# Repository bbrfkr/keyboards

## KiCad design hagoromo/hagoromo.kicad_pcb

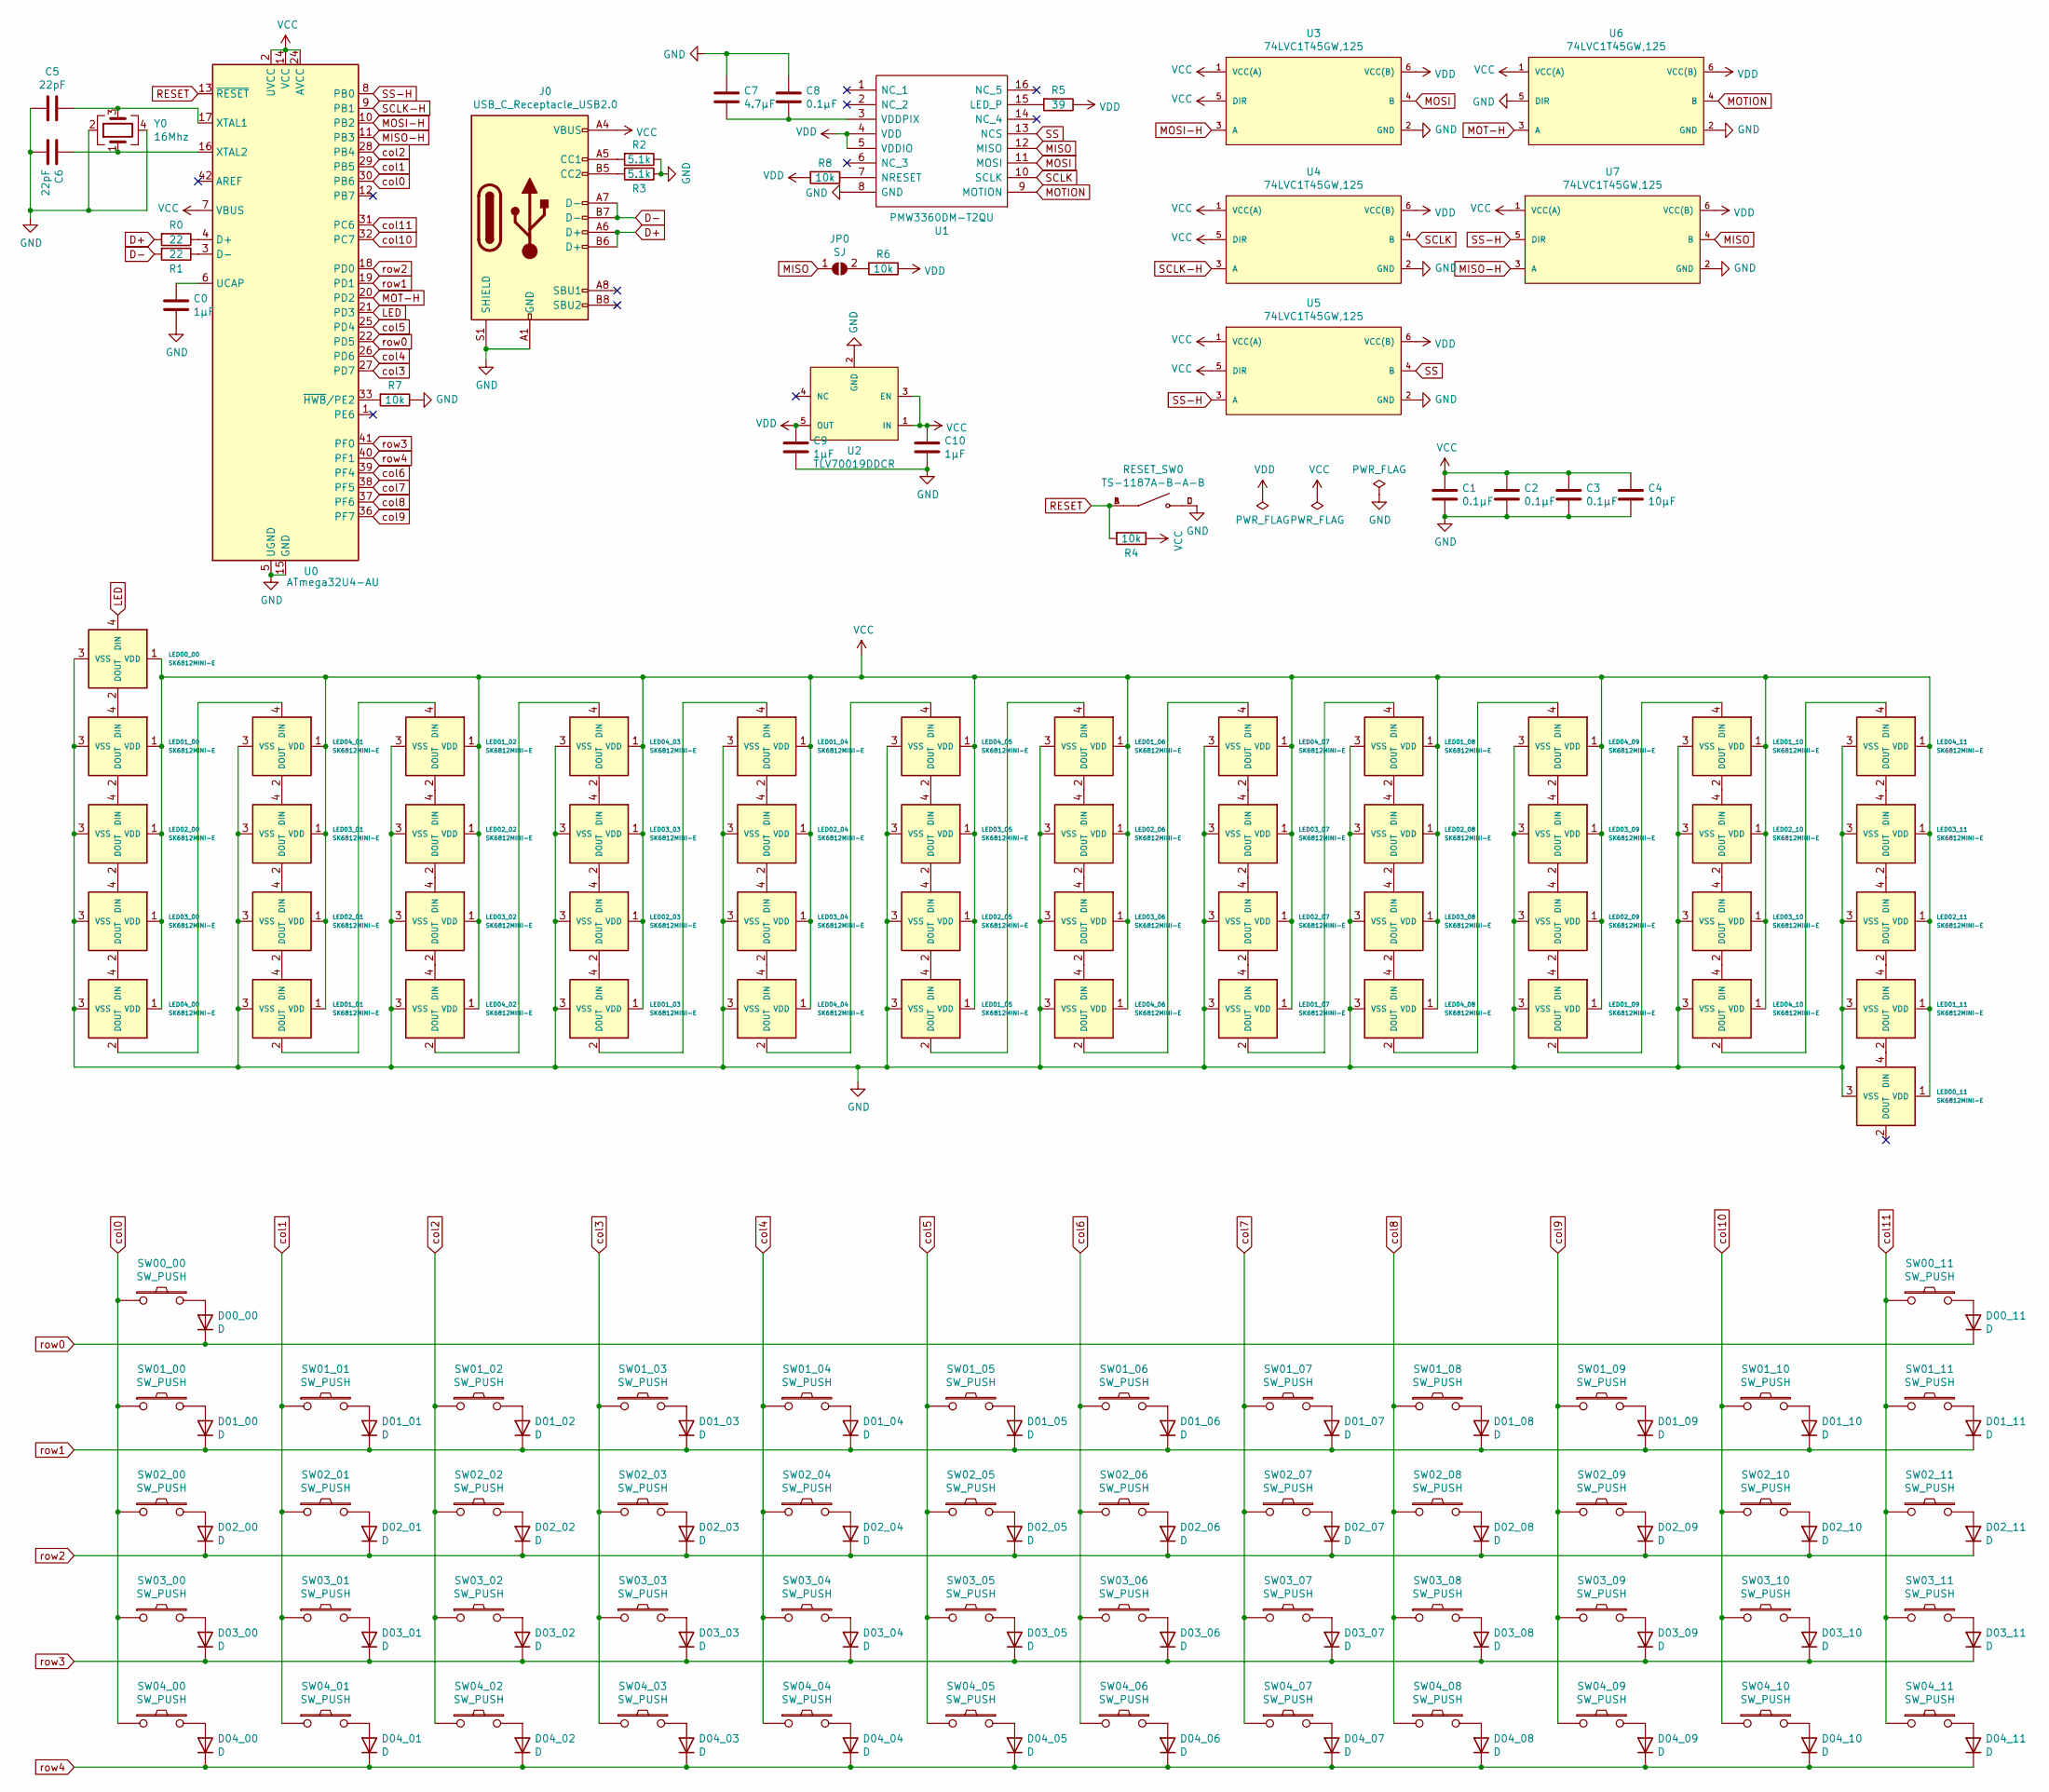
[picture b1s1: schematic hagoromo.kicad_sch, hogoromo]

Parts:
C0, C9, C10: 1μF; C_1206_3216Metric
C1, C2, C3, C8: 0.1μF; C_1206_3216Metric
C4: 10μF; C_1206_3216Metric
C5, C6: 22pF; C_1206_3216Metric
C7: 4.7μF; C_1206_3216Metric
D00_00, D00_11, D01_00, D01_01, D01_02, D01_03, D01_04, D01_05, D01_06, D01_07, D01_08, D01_09, D01_10, D01_11, D02_00, D02_01, D02_02, D02_03, D02_04, D02_05, D02_06, D02_07, D02_08, D02_09, D02_10, D02_11, D03_00, D03_01, D03_02, D03_03, D03_04, D03_05, D03_06, D03_07, D03_08, D03_09, D03_10, D03_11, D04_00, D04_01, D04_02, D04_03, D04_04, D04_05, D04_06, D04_07, D04_08, D04_09, D04_10, D04_11: D; D_SOD-123
J0: USB_C_Receptacle_USB2.0; USB_C_Receptacle_HRO_TYPE-C-31-M-12
JP0: SJ; SolderJumper-2_P1.3mm_Open_Pad1.0x1.5mm
LED00_00, LED00_11, LED01_00, LED01_01, LED01_02, LED01_03, LED01_04, LED01_05, LED01_06, LED01_07, LED01_08, LED01_09, LED01_10, LED01_11, LED02_00, LED02_01, LED02_02, LED02_03, LED02_04, LED02_05, LED02_06, LED02_07, LED02_08, LED02_09, LED02_10, LED02_11, LED03_00, LED03_01, LED03_02, LED03_03, LED03_04, LED03_05, LED03_06, LED03_07, LED03_08, LED03_09, LED03_10, LED03_11, LED04_00, LED04_01, LED04_02, LED04_03, LED04_04, LED04_05, LED04_06, LED04_07, LED04_08, LED04_09, LED04_10, LED04_11: SK6812MINI-E; SK6812-MINI-E
R0, R1: 22; R_1206_3216Metric
R2, R3: 5.1k; R_1206_3216Metric
R4, R6, R7, R8: 10k; R_1206_3216Metric
R5: 39; R_1206_3216Metric
RESET_SW0: TS-1187A-B-A-B; SW_TS-1187A-B-A-B; PARTREV A0
SW00_00, SW00_11, SW01_01, SW01_02, SW01_03, SW01_04, SW01_05, SW01_06, SW01_07, SW01_08, SW01_09, SW01_10, SW02_01, SW02_02, SW02_03, SW02_04, SW02_05, SW02_06, SW02_07, SW02_08, SW02_09, SW02_10, SW03_01, SW03_02, SW03_03, SW03_04, SW03_05, SW03_06, SW03_07, SW03_08, SW03_09, SW03_10, SW04_03, SW04_04, SW04_05, SW04_06, SW04_07, SW04_08: SW_PUSH; SW_Hotswap_Kailh_1.00u
SW01_00, SW01_11: SW_PUSH; SW_Hotswap_Kailh_1.50u
SW02_00: SW_PUSH; SW_Hotswap_Kailh_1.75u
SW02_11, SW03_00: SW_PUSH; SW_Hotswap_Kailh_2.25u
SW03_11: SW_PUSH; SW_Hotswap_Kailh_2.75u
SW04_00, SW04_01, SW04_02, SW04_09, SW04_10, SW04_11: SW_PUSH; SW_Hotswap_Kailh_1.25u
U0: ATmega32U4-AU; TQFP-44_10x10mm_P0.8mm
U1: PMW3360DM-T2QU; PMW3360; Manufacturer_Part_Number PMW3360DM-T2QU
U2: TLV70019DDCR; Texas_Instruments-TLV70019DDCR-Level_A
U3, U4, U5, U6, U7: 74LVC1T45GW,125; Nexperia-SOT363-11_2018-0-IPC_A; mouser part number 771-74LVC1T45GW125; digikey description IC TRNSLTR BIDIRECTIONAL 6TSSOP
Y0: 16Mhz; Crystal_SMD_SeikoEpson_FA238-4Pin_3.2x2.5mm

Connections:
D+: J0.A6 (D+), J0.B6 (D+), R0.2
D-: J0.A7 (D-), J0.B7 (D-), R1.2
GND: C0.2, C1.2, C2.2, C3.2, C4.2, C5.1, C6.2, C7.1, C8.1, C9.2, C10.2, J0.A1 (GND), J0.A12 (GND), J0.B1 (GND), J0.B12 (GND), J0.S1 (SHIELD), LED00_00.3 (VSS), LED00_11.3 (VSS), LED01_00.3 (VSS), LED01_01.3 (VSS), LED01_02.3 (VSS), LED01_03.3 (VSS), LED01_04.3 (VSS), LED01_05.3 (VSS), LED01_06.3 (VSS), LED01_07.3 (VSS), LED01_08.3 (VSS), LED01_09.3 (VSS), LED01_10.3 (VSS), LED01_11.3 (VSS), LED02_00.3 (VSS), LED02_01.3 (VSS), LED02_02.3 (VSS), LED02_03.3 (VSS), LED02_04.3 (VSS), LED02_05.3 (VSS), LED02_06.3 (VSS), LED02_07.3 (VSS), LED02_08.3 (VSS), LED02_09.3 (VSS), LED02_10.3 (VSS), LED02_11.3 (VSS), LED03_00.3 (VSS), LED03_01.3 (VSS), LED03_02.3 (VSS), LED03_03.3 (VSS), LED03_04.3 (VSS), LED03_05.3 (VSS), LED03_06.3 (VSS), LED03_07.3 (VSS), LED03_08.3 (VSS), LED03_09.3 (VSS), LED03_10.3 (VSS), LED03_11.3 (VSS), LED04_00.3 (VSS), LED04_01.3 (VSS), LED04_02.3 (VSS), LED04_03.3 (VSS), LED04_04.3 (VSS), LED04_05.3 (VSS), LED04_06.3 (VSS), LED04_07.3 (VSS), LED04_08.3 (VSS), LED04_09.3 (VSS), LED04_10.3 (VSS), LED04_11.3 (VSS), R2.1, R3.1, R7.1, RESET_SW0.C, RESET_SW0.D, U0.5 (UGND), U0.15 (GND), U0.23 (GND), U0.35 (GND), U0.43 (GND), U1.8 (GND), U2.2 (GND), U3.2 (GND), U4.2 (GND), U5.2 (GND), U6.2 (GND), U6.5 (DIR), U7.2 (GND), Y0.2, Y0.4
LED: LED00_00.4 (DIN), U0.21 (PD3)
MISO: JP0.1 (A), U1.12 (MISO), U7.4 (B)
MISO-H: U0.11 (PB3), U7.3 (A)
MOSI: U1.11 (MOSI), U3.4 (B)
MOSI-H: U0.10 (PB2), U3.3 (A)
MOT-H: U0.20 (PD2), U6.3 (A)
MOTION: U1.9 (MOTION), U6.4 (B)
unnamed: C0.1, U0.6 (UCAP)
unnamed: C5.2, U0.17 (XTAL1), Y0.3
unnamed: C6.1, U0.16 (XTAL2), Y0.1
unnamed: C7.2, C8.2, U1.3 (VDDPIX)
unnamed: D00_00.2 (A), SW00_00.2
unnamed: D00_11.2 (A), SW00_11.2
unnamed: D01_00.2 (A), SW01_00.2
unnamed: D01_01.2 (A), SW01_01.2
unnamed: D01_02.2 (A), SW01_02.2
unnamed: D01_03.2 (A), SW01_03.2
unnamed: D01_04.2 (A), SW01_04.2
unnamed: D01_05.2 (A), SW01_05.2
unnamed: D01_06.2 (A), SW01_06.2
unnamed: D01_07.2 (A), SW01_07.2
unnamed: D01_08.2 (A), SW01_08.2
unnamed: D01_09.2 (A), SW01_09.2
unnamed: D01_10.2 (A), SW01_10.2
unnamed: D01_11.2 (A), SW01_11.2
unnamed: D02_00.2 (A), SW02_00.2
unnamed: D02_01.2 (A), SW02_01.2
unnamed: D02_02.2 (A), SW02_02.2
unnamed: D02_03.2 (A), SW02_03.2
unnamed: D02_04.2 (A), SW02_04.2
unnamed: D02_05.2 (A), SW02_05.2
unnamed: D02_06.2 (A), SW02_06.2
unnamed: D02_07.2 (A), SW02_07.2
unnamed: D02_08.2 (A), SW02_08.2
unnamed: D02_09.2 (A), SW02_09.2
unnamed: D02_10.2 (A), SW02_10.2
unnamed: D02_11.2 (A), SW02_11.2
unnamed: D03_00.2 (A), SW03_00.2
unnamed: D03_01.2 (A), SW03_01.2
unnamed: D03_02.2 (A), SW03_02.2
unnamed: D03_03.2 (A), SW03_03.2
unnamed: D03_04.2 (A), SW03_04.2
unnamed: D03_05.2 (A), SW03_05.2
unnamed: D03_06.2 (A), SW03_06.2
unnamed: D03_07.2 (A), SW03_07.2
unnamed: D03_08.2 (A), SW03_08.2
unnamed: D03_09.2 (A), SW03_09.2
unnamed: D03_10.2 (A), SW03_10.2
unnamed: D03_11.2 (A), SW03_11.2
unnamed: D04_00.2 (A), SW04_00.2
unnamed: D04_01.2 (A), SW04_01.2
unnamed: D04_02.2 (A), SW04_02.2
unnamed: D04_03.2 (A), SW04_03.2
unnamed: D04_04.2 (A), SW04_04.2
unnamed: D04_05.2 (A), SW04_05.2
unnamed: D04_06.2 (A), SW04_06.2
unnamed: D04_07.2 (A), SW04_07.2
unnamed: D04_08.2 (A), SW04_08.2
unnamed: D04_09.2 (A), SW04_09.2
unnamed: D04_10.2 (A), SW04_10.2
unnamed: D04_11.2 (A), SW04_11.2
unnamed: J0.A5 (CC1), R2.2
unnamed: J0.B5 (CC2), R3.2
unnamed: JP0.2 (B), R6.2
unnamed: LED00_00.2 (DOUT), LED01_00.4 (DIN)
unnamed: LED00_11.4 (DIN), LED01_11.2 (DOUT)
unnamed: LED01_00.2 (DOUT), LED02_00.4 (DIN)
unnamed: LED01_01.2 (DOUT), LED01_02.4 (DIN)
unnamed: LED01_01.4 (DIN), LED02_01.2 (DOUT)
unnamed: LED01_02.2 (DOUT), LED02_02.4 (DIN)
unnamed: LED01_03.2 (DOUT), LED01_04.4 (DIN)
unnamed: LED01_03.4 (DIN), LED02_03.2 (DOUT)
unnamed: LED01_04.2 (DOUT), LED02_04.4 (DIN)
unnamed: LED01_05.2 (DOUT), LED01_06.4 (DIN)
unnamed: LED01_05.4 (DIN), LED02_05.2 (DOUT)
unnamed: LED01_06.2 (DOUT), LED02_06.4 (DIN)
unnamed: LED01_07.2 (DOUT), LED01_08.4 (DIN)
unnamed: LED01_07.4 (DIN), LED02_07.2 (DOUT)
unnamed: LED01_08.2 (DOUT), LED02_08.4 (DIN)
unnamed: LED01_09.2 (DOUT), LED01_10.4 (DIN)
unnamed: LED01_09.4 (DIN), LED02_09.2 (DOUT)
unnamed: LED01_10.2 (DOUT), LED02_10.4 (DIN)
unnamed: LED01_11.4 (DIN), LED02_11.2 (DOUT)
unnamed: LED02_00.2 (DOUT), LED03_00.4 (DIN)
unnamed: LED02_01.4 (DIN), LED03_01.2 (DOUT)
unnamed: LED02_02.2 (DOUT), LED03_02.4 (DIN)
unnamed: LED02_03.4 (DIN), LED03_03.2 (DOUT)
unnamed: LED02_04.2 (DOUT), LED03_04.4 (DIN)
unnamed: LED02_05.4 (DIN), LED03_05.2 (DOUT)
unnamed: LED02_06.2 (DOUT), LED03_06.4 (DIN)
unnamed: LED02_07.4 (DIN), LED03_07.2 (DOUT)
unnamed: LED02_08.2 (DOUT), LED03_08.4 (DIN)
unnamed: LED02_09.4 (DIN), LED03_09.2 (DOUT)
unnamed: LED02_10.2 (DOUT), LED03_10.4 (DIN)
unnamed: LED02_11.4 (DIN), LED03_11.2 (DOUT)
unnamed: LED03_00.2 (DOUT), LED04_00.4 (DIN)
unnamed: LED03_01.4 (DIN), LED04_01.2 (DOUT)
unnamed: LED03_02.2 (DOUT), LED04_02.4 (DIN)
unnamed: LED03_03.4 (DIN), LED04_03.2 (DOUT)
unnamed: LED03_04.2 (DOUT), LED04_04.4 (DIN)
unnamed: LED03_05.4 (DIN), LED04_05.2 (DOUT)
unnamed: LED03_06.2 (DOUT), LED04_06.4 (DIN)
unnamed: LED03_07.4 (DIN), LED04_07.2 (DOUT)
unnamed: LED03_08.2 (DOUT), LED04_08.4 (DIN)
unnamed: LED03_09.4 (DIN), LED04_09.2 (DOUT)
unnamed: LED03_10.2 (DOUT), LED04_10.4 (DIN)
unnamed: LED03_11.4 (DIN), LED04_11.2 (DOUT)
unnamed: LED04_00.2 (DOUT), LED04_01.4 (DIN)
unnamed: LED04_02.2 (DOUT), LED04_03.4 (DIN)
unnamed: LED04_04.2 (DOUT), LED04_05.4 (DIN)
unnamed: LED04_06.2 (DOUT), LED04_07.4 (DIN)
unnamed: LED04_08.2 (DOUT), LED04_09.4 (DIN)
unnamed: LED04_10.2 (DOUT), LED04_11.4 (DIN)
unnamed: R0.1, U0.4 (D+)
unnamed: R1.1, U0.3 (D-)
unnamed: R5.2, U1.15 (LED_P)
unnamed: R7.2, U0.33 (~HWB/PE2)
unnamed: R8.1, U1.7 (NRESET)
RESET: R4.2, RESET_SW0.A, RESET_SW0.B, U0.13 (~RESET)
SCLK: U1.10 (SCLK), U4.4 (B)
SCLK-H: U0.9 (PB1), U4.3 (A)
SS: U1.13 (NCS), U5.4 (B)
SS-H: U0.8 (PB0), U5.3 (A), U7.5 (DIR)
VCC: C1.1, C2.1, C3.1, C4.1, C10.1, J0.A4 (VBUS), J0.A9 (VBUS), J0.B4 (VBUS), J0.B9 (VBUS), LED00_00.1 (VDD), LED00_11.1 (VDD), LED01_00.1 (VDD), LED01_01.1 (VDD), LED01_02.1 (VDD), LED01_03.1 (VDD), LED01_04.1 (VDD), LED01_05.1 (VDD), LED01_06.1 (VDD), LED01_07.1 (VDD), LED01_08.1 (VDD), LED01_09.1 (VDD), LED01_10.1 (VDD), LED01_11.1 (VDD), LED02_00.1 (VDD), LED02_01.1 (VDD), LED02_02.1 (VDD), LED02_03.1 (VDD), LED02_04.1 (VDD), LED02_05.1 (VDD), LED02_06.1 (VDD), LED02_07.1 (VDD), LED02_08.1 (VDD), LED02_09.1 (VDD), LED02_10.1 (VDD), LED02_11.1 (VDD), LED03_00.1 (VDD), LED03_01.1 (VDD), LED03_02.1 (VDD), LED03_03.1 (VDD), LED03_04.1 (VDD), LED03_05.1 (VDD), LED03_06.1 (VDD), LED03_07.1 (VDD), LED03_08.1 (VDD), LED03_09.1 (VDD), LED03_10.1 (VDD), LED03_11.1 (VDD), LED04_00.1 (VDD), LED04_01.1 (VDD), LED04_02.1 (VDD), LED04_03.1 (VDD), LED04_04.1 (VDD), LED04_05.1 (VDD), LED04_06.1 (VDD), LED04_07.1 (VDD), LED04_08.1 (VDD), LED04_09.1 (VDD), LED04_10.1 (VDD), LED04_11.1 (VDD), R4.1, U0.2 (UVCC), U0.7 (VBUS), U0.14 (VCC), U0.24 (AVCC), U0.34 (VCC), U0.44 (AVCC), U2.1 (IN), U2.3 (EN), U3.1 (VCC(A)), U3.5 (DIR), U4.1 (VCC(A)), U4.5 (DIR), U5.1 (VCC(A)), U5.5 (DIR), U6.1 (VCC(A)), U7.1 (VCC(A))
VDD: C9.1, R5.1, R6.1, R8.2, U1.4 (VDD), U1.5 (VDDIO), U2.5 (OUT), U3.6 (VCC(B)), U4.6 (VCC(B)), U5.6 (VCC(B)), U6.6 (VCC(B)), U7.6 (VCC(B))
col0: SW00_00.1, SW01_00.1, SW02_00.1, SW03_00.1, SW04_00.1, U0.30 (PB6)
col1: SW01_01.1, SW02_01.1, SW03_01.1, SW04_01.1, U0.29 (PB5)
col2: SW01_02.1, SW02_02.1, SW03_02.1, SW04_02.1, U0.28 (PB4)
col3: SW01_03.1, SW02_03.1, SW03_03.1, SW04_03.1, U0.27 (PD7)
col4: SW01_04.1, SW02_04.1, SW03_04.1, SW04_04.1, U0.26 (PD6)
col5: SW01_05.1, SW02_05.1, SW03_05.1, SW04_05.1, U0.25 (PD4)
col6: SW01_06.1, SW02_06.1, SW03_06.1, SW04_06.1, U0.39 (PF4)
col7: SW01_07.1, SW02_07.1, SW03_07.1, SW04_07.1, U0.38 (PF5)
col8: SW01_08.1, SW02_08.1, SW03_08.1, SW04_08.1, U0.37 (PF6)
col9: SW01_09.1, SW02_09.1, SW03_09.1, SW04_09.1, U0.36 (PF7)
col10: SW01_10.1, SW02_10.1, SW03_10.1, SW04_10.1, U0.32 (PC7)
col11: SW00_11.1, SW01_11.1, SW02_11.1, SW03_11.1, SW04_11.1, U0.31 (PC6)
row0: D00_00.1 (K), D00_11.1 (K), U0.22 (PD5)
row1: D01_00.1 (K), D01_01.1 (K), D01_02.1 (K), D01_03.1 (K), D01_04.1 (K), D01_05.1 (K), D01_06.1 (K), D01_07.1 (K), D01_08.1 (K), D01_09.1 (K), D01_10.1 (K), D01_11.1 (K), U0.19 (PD1)
row2: D02_00.1 (K), D02_01.1 (K), D02_02.1 (K), D02_03.1 (K), D02_04.1 (K), D02_05.1 (K), D02_06.1 (K), D02_07.1 (K), D02_08.1 (K), D02_09.1 (K), D02_10.1 (K), D02_11.1 (K), U0.18 (PD0)
row3: D03_00.1 (K), D03_01.1 (K), D03_02.1 (K), D03_03.1 (K), D03_04.1 (K), D03_05.1 (K), D03_06.1 (K), D03_07.1 (K), D03_08.1 (K), D03_09.1 (K), D03_10.1 (K), D03_11.1 (K), U0.41 (PF0)
row4: D04_00.1 (K), D04_01.1 (K), D04_02.1 (K), D04_03.1 (K), D04_04.1 (K), D04_05.1 (K), D04_06.1 (K), D04_07.1 (K), D04_08.1 (K), D04_09.1 (K), D04_10.1 (K), D04_11.1 (K), U0.40 (PF1)

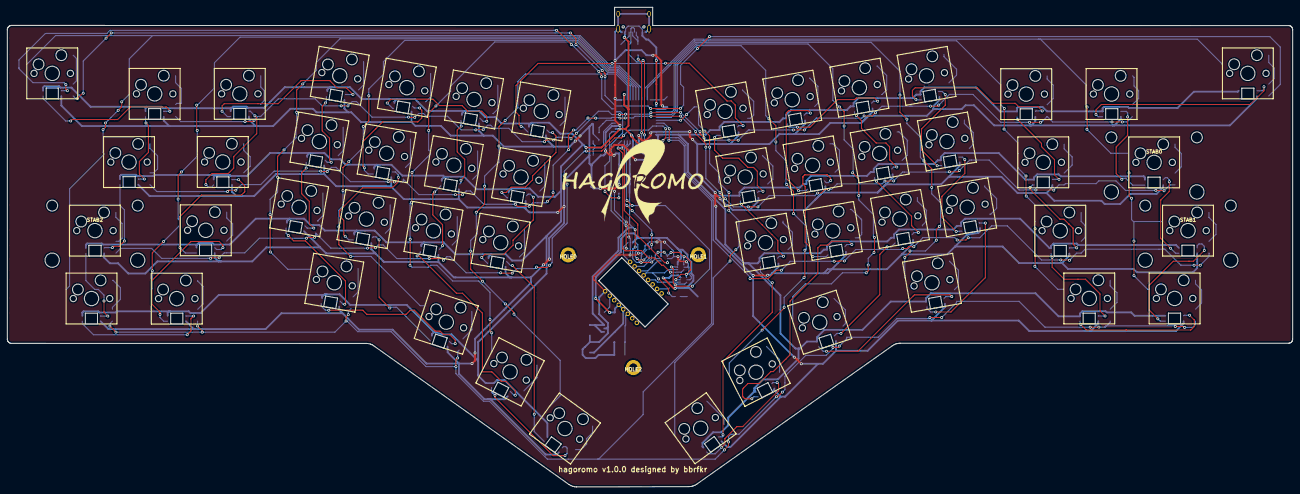
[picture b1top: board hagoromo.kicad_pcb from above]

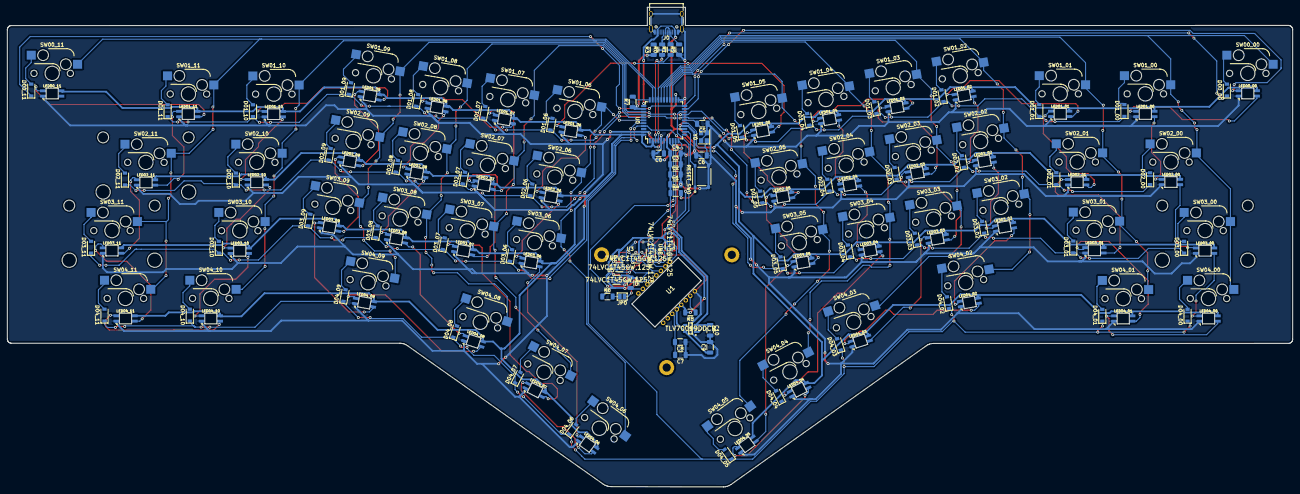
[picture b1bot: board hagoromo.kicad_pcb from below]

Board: 2 copper layers, 358.9 x 133.9 mm, 189 parts (132 on the bottom side), 145 nets.

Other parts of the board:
HOLE0, HOLE1, HOLE2: M2_Hole_TH
LOGO0: LOGO; logo
STAB0, STAB1, STAB2: Stabilizer_Cherry_MX_2u

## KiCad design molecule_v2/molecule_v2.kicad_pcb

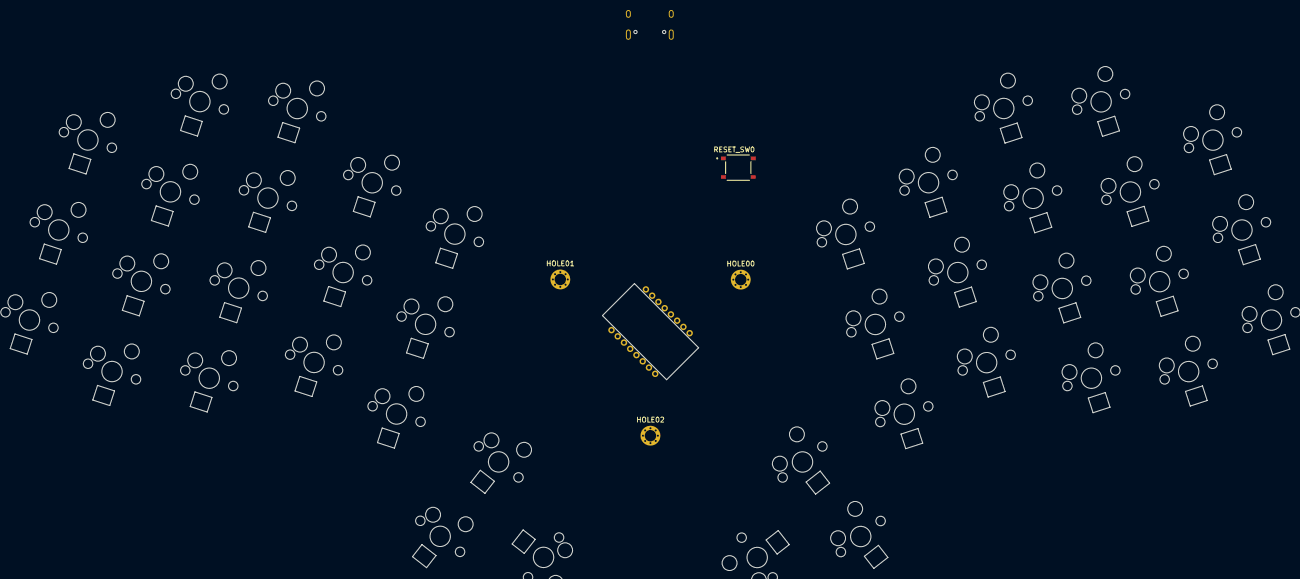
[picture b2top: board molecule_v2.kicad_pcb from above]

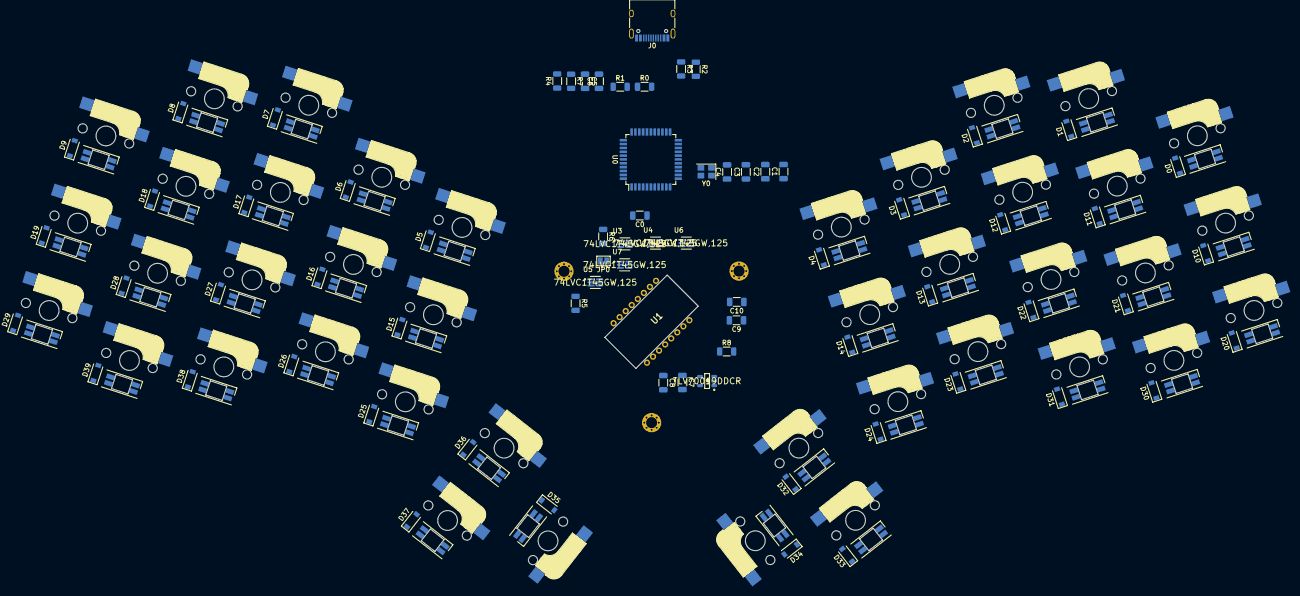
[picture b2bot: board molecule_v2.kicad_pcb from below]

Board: 2 copper layers, 156 parts (111 on the bottom side), 122 nets, no tracks yet.

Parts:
C0, C9, C10: 1μF; C_1206_3216Metric
C1, C2, C3, C8: 0.1μF; C_1206_3216Metric
C4: 10μF; C_1206_3216Metric
C5, C6: 22pF; C_1206_3216Metric
C7: 4.7μF; C_1206_3216Metric
D0, D1, D2, D3, D4, D5, D6, D7, D8, D9, D10, D11, D12, D13, D14, D15, D16, D17, D18, D19, D20, D21, D22, D23, D24, D25, D26, D27, D28, D29, D30, D31, D32, D33, D34, D35, D36, D37, D38, D39: D; D_SOD-123
HOLE00, HOLE01, HOLE02: Val**; M2_HOLE_v3
J0: USB_C_Receptacle_USB2.0; USB_C_Receptacle_HRO_TYPE-C-31-M-12
JP0: SJ; SolderJumper-2_P1.3mm_Open_Pad1.0x1.5mm
LED0, LED1, LED2, LED3, LED4, LED5, LED6, LED7, LED8, LED9, LED10, LED11, LED12, LED13, LED14, LED15, LED16, LED17, LED18, LED19, LED20, LED21, LED22, LED23, LED24, LED25, LED26, LED27, LED28, LED29, LED30, LED31, LED32, LED33, LED34, LED35, LED36, LED37, LED38, LED39: YS-SK6812MINI-E
LOGO01: LOGO; molecule-logo
R0, R1: 22; R_1206_3216Metric
R2, R3: 5.1k; R_1206_3216Metric
R4, R6, R7, R8: 10k; R_1206_3216Metric
R5: 39; R_1206_3216Metric
RESET_SW0: TS-1187A-B-A-B; SW_TS-1187A-B-A-B
SW0, SW1, SW2, SW3, SW4, SW5, SW6, SW7, SW8, SW9, SW10, SW11, SW12, SW13, SW14, SW15, SW16, SW17, SW18, SW19, SW20, SW21, SW22, SW23, SW24, SW25, SW26, SW27, SW28, SW29, SW30, SW31, SW32, SW33, SW36, SW37, SW38, SW39: SW_PUSH; CherryMX_Hotswap
SW34, SW35: SW_PUSH; CherryMX_Hotswap_1.5u
U0: ATmega32U4-AU; TQFP-44_10x10mm_P0.8mm
U1: PMW3360DM-T2QU; PMW3360
U2: TLV70019DDCR; Texas_Instruments-TLV70019DDCR-Level_A
U3, U4, U5, U6, U7: 74LVC1T45GW,125; Nexperia-SOT363-11_2018-0-IPC_A
Y0: 16Mhz; Crystal_SMD_SeikoEpson_FA238-4Pin_3.2x2.5mm

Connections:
D+: J0.A6, J0.B6, R0.2
D-: J0.A7, J0.B7, R1.2
GND: C0.2, C1.2, C2.2, C3.2, C4.2, C5.1, C6.2, C7.1, C8.1, C9.2, C10.2, J0.A1, J0.A12, J0.B1, J0.B12, J0.S1, LED0.3, LED1.3, LED2.3, LED3.3, LED4.3, LED5.3, LED6.3, LED7.3, LED8.3, LED9.3, LED10.3, LED11.3, LED12.3, LED13.3, LED14.3, LED15.3, LED16.3, LED17.3, LED18.3, LED19.3, LED20.3, LED21.3, LED22.3, LED23.3, LED24.3, LED25.3, LED26.3, LED27.3, LED28.3, LED29.3, LED30.3, LED31.3, LED32.3, LED33.3, LED34.3, LED35.3, LED36.3, LED37.3, LED38.3, LED39.3, R2.1, R3.1, R7.1, RESET_SW0.C, RESET_SW0.D, U0.5, U0.15, U0.23, U0.35, U0.43, U1.8, U2.2, U3.2, U4.2, U5.2, U6.2, U6.5, U7.2, Y0.2, Y0.4
LED: LED0.4, U0.21
MISO: JP0.1, U1.12, U7.4
MISO-H: U0.11, U7.3
MOSI: U1.11, U3.4
MOSI-H: U0.10, U3.3
MOT-H: U0.20, U6.3
MOTION: U1.9, U6.4
unnamed: C0.1, U0.6
unnamed: C5.2, U0.17, Y0.3
unnamed: C6.1, U0.16, Y0.1
unnamed: C7.2, C8.2, U1.3
unnamed: D0.2, SW0.2
unnamed: D1.2, SW1.2
unnamed: D2.2, SW2.2
unnamed: D3.2, SW3.2
unnamed: D4.2, SW4.2
unnamed: D5.2, SW5.2
unnamed: D6.2, SW6.2
unnamed: D7.2, SW7.2
unnamed: D8.2, SW8.2
unnamed: D9.2, SW9.2
unnamed: D10.2, SW10.2
unnamed: D11.2, SW11.2
unnamed: D12.2, SW12.2
unnamed: D13.2, SW13.2
unnamed: D14.2, SW14.2
unnamed: D15.2, SW15.2
unnamed: D16.2, SW16.2
unnamed: D17.2, SW17.2
unnamed: D18.2, SW18.2
unnamed: D19.2, SW19.2
unnamed: D20.2, SW20.2
unnamed: D21.2, SW21.2
unnamed: D22.2, SW22.2
unnamed: D23.2, SW23.2
unnamed: D24.2, SW24.2
unnamed: D25.2, SW25.2
unnamed: D26.2, SW26.2
unnamed: D27.2, SW27.2
unnamed: D28.2, SW28.2
unnamed: D29.2, SW29.2
unnamed: D30.2, SW30.2
unnamed: D31.2, SW31.2
unnamed: D32.2, SW32.2
unnamed: D33.2, SW33.2
unnamed: D34.2, SW34.2
unnamed: D35.2, SW35.2
unnamed: D36.2, SW36.2
unnamed: D37.2, SW37.2
unnamed: D38.2, SW38.2
unnamed: D39.2, SW39.2
unnamed: J0.A5, R2.2
unnamed: J0.B5, R3.2
unnamed: JP0.2, R6.2
unnamed: LED0.2, LED10.4
unnamed: LED1.2, LED2.4
unnamed: LED1.4, LED11.2
unnamed: LED3.2, LED4.4
unnamed: LED5.2, LED6.4
unnamed: LED7.2, LED8.4
unnamed: LED10.2, LED20.4
unnamed: LED11.4, LED21.2
unnamed: LED12.2, LED22.4
unnamed: LED2.2, LED12.4
unnamed: LED3.4, LED13.2
unnamed: LED13.4, LED23.2
unnamed: LED14.2, LED24.4
unnamed: LED4.2, LED14.4
unnamed: LED5.4, LED15.2
unnamed: LED15.4, LED25.2
unnamed: LED16.2, LED26.4
unnamed: LED6.2, LED16.4
unnamed: LED7.4, LED17.2
unnamed: LED17.4, LED27.2
unnamed: LED18.2, LED28.4
unnamed: LED8.2, LED18.4
unnamed: LED9.4, LED19.2
unnamed: LED19.4, LED29.2
unnamed: LED20.2, LED30.4
unnamed: LED21.4, LED31.2
unnamed: LED22.2, LED32.4
unnamed: LED23.4, LED33.2
unnamed: LED24.2, LED34.4
unnamed: LED25.4, LED35.2
unnamed: LED26.2, LED36.4
unnamed: LED27.4, LED37.2
unnamed: LED28.2, LED38.4
unnamed: LED29.4, LED39.2
unnamed: LED30.2, LED31.4
unnamed: LED32.2, LED33.4
unnamed: LED34.2, LED35.4
unnamed: LED36.2, LED37.4
unnamed: LED38.2, LED39.4
unnamed: R0.1, U0.4
unnamed: R1.1, U0.3
unnamed: R5.2, U1.15
unnamed: R7.2, U0.33
unnamed: R8.1, U1.7
RESET: R4.2, RESET_SW0.A, RESET_SW0.B, U0.13
SCLK: U1.10, U4.4
SCLK-H: U0.9, U4.3
SS: U1.13, U5.4
SS-H: U0.8, U5.3, U7.5
VCC: C1.1, C2.1, C3.1, C4.1, C10.1, J0.A4, J0.A9, J0.B4, J0.B9, LED0.1, LED1.1, LED2.1, LED3.1, LED4.1, LED5.1, LED6.1, LED7.1, LED8.1, LED9.1, LED10.1, LED11.1, LED12.1, LED13.1, LED14.1, LED15.1, LED16.1, LED17.1, LED18.1, LED19.1, LED20.1, LED21.1, LED22.1, LED23.1, LED24.1, LED25.1, LED26.1, LED27.1, LED28.1, LED29.1, LED30.1, LED31.1, LED32.1, LED33.1, LED34.1, LED35.1, LED36.1, LED37.1, LED38.1, LED39.1, R4.1, U0.2, U0.7, U0.14, U0.24, U0.34, U0.44, U2.1, U2.3, U3.1, U3.5, U4.1, U4.5, U5.1, U5.5, U6.1, U7.1
VDD: C9.1, R5.1, R6.1, R8.2, U1.4, U1.5, U2.5, U3.6, U4.6, U5.6, U6.6, U7.6
col0: SW0.1, SW10.1, SW20.1, SW30.1, U0.29
col1: SW1.1, SW11.1, SW21.1, SW31.1, U0.28
col2: SW2.1, SW12.1, SW22.1, SW32.1, U0.27
col3: SW3.1, SW13.1, SW23.1, SW33.1, U0.26
col4: SW4.1, SW14.1, SW24.1, SW34.1, U0.25
col5: SW5.1, SW15.1, SW25.1, SW35.1, U0.41
col6: SW6.1, SW16.1, SW26.1, SW36.1, U0.40
col7: SW7.1, SW17.1, SW27.1, SW37.1, U0.39
col8: SW8.1, SW18.1, SW28.1, SW38.1, U0.38
col9: SW9.1, SW19.1, SW29.1, SW39.1, U0.37
row0: D0.1, D1.1, D2.1, D3.1, D4.1, D5.1, D6.1, D7.1, D8.1, D9.1, U0.22
row1: D10.1, D11.1, D12.1, D13.1, D14.1, D15.1, D16.1, D17.1, D18.1, D19.1, U0.19
row2: D20.1, D21.1, D22.1, D23.1, D24.1, D25.1, D26.1, D27.1, D28.1, D29.1, U0.18
row3: D30.1, D31.1, D32.1, D33.1, D34.1, D35.1, D36.1, D37.1, D38.1, D39.1, U0.12

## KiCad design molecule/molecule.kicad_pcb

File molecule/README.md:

# molecule - 40%一体型トラックボールキーボード
moleculeは以下の特徴を持つ、40%キーボードです。

- columnar-staggered
- 小指に無理をさせず、かつ親指を内側に入れる配置を避けるように意識したキー配列
- トラックボールを内包し、ホームポジションから手を動かさずにポインティングも可能
- Cherry MXスイッチに正式対応（追加はんだ付けでKailh Chocスイッチにも対応可能）

## 最新バージョン

## キーマップ
デフォルトで書き込まれているキーマップは以下のPDFの通りになります。また、[QMK Configurator](https://config.qmk.fm/#/molecule/LAYOUT)を用いて、キーマップをカスタマイズすることが可能です。

- [molecule デフォルトキーマップ](https://github.com/bbrfkr/keyboards/blob/master/molecule/molecule-default-keymap.pdf)

## 謝辞
本プロジェクトは[aball](https://github.com/brickbots/aball)プロジェクトから無制限利用許諾をいただき、部分的に当プロジェクト内容を含んでおります。この場を借りて御礼申し上げます。

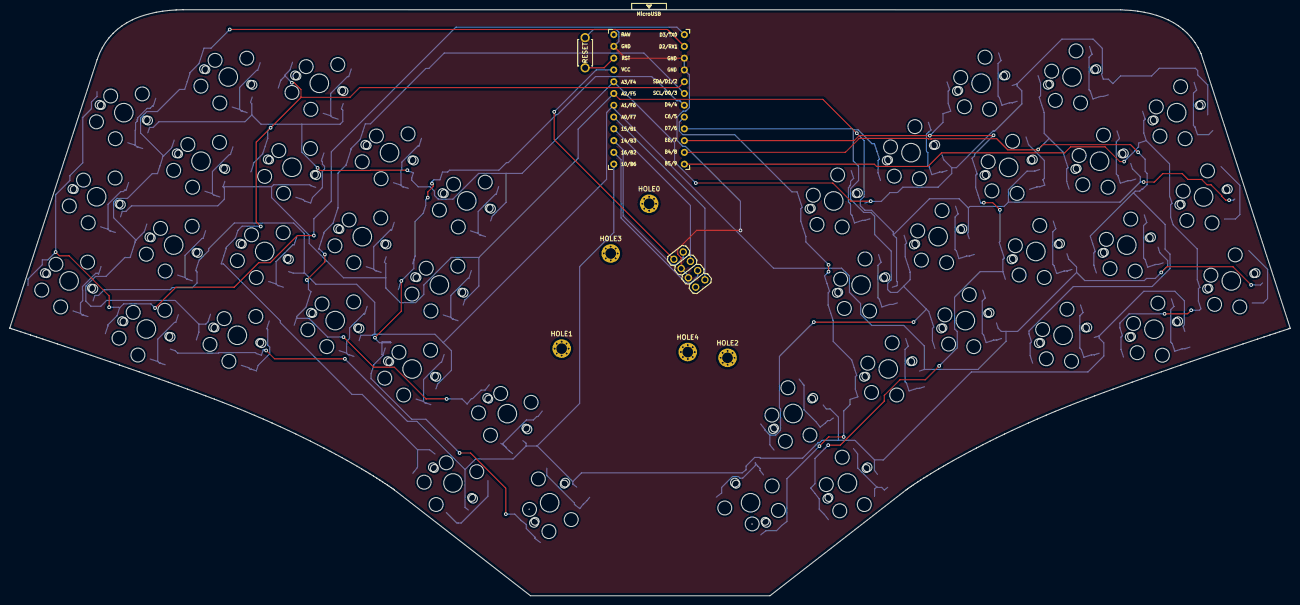
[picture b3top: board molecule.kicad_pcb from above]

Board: 2 copper layers, 276.2 x 126.4 mm, 88 parts (0 on the bottom side), 61 nets.

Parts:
D0, D1, D2, D3, D4, D5, D6, D7, D8, D9, D10, D11, D12, D13, D14, D15, D16, D17, D18, D19, D20, D21, D22, D23, D24, D25, D26, D27, D28, D29, D30, D31, D32, D33, D34, D35, D36, D37, D38, D39: DIODE; D3_SMD
HOLE0, HOLE1, HOLE2, HOLE3, HOLE4: Val**; M2_HOLE_v3
JP0: PINHD-2X4; 2X04
RSSW0: SW_PUSH; ResetSW_1side
SW0, SW1, SW2, SW3, SW4, SW5, SW6, SW7, SW8, SW9, SW10, SW11, SW12, SW13, SW14, SW15, SW16, SW17, SW18, SW19, SW20, SW21, SW22, SW23, SW24, SW25, SW26, SW27, SW28, SW29, SW30, SW31, SW32, SW33, SW36, SW37, SW38, SW39: SW_PUSH; CherryMX_Choc_Hotswap
SW34, SW35: SW_PUSH; CherryMX_Choc_Hotswap_1.5u
U0: ProMicro; ProMicro_v3

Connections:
GND: JP0.3, JP0.5, RSSW0.2, U0.3, U0.4, U0.23
MI: JP0.2, U0.15
MO: JP0.6, U0.14
unnamed: D0.1, SW0.2
unnamed: D1.1, SW1.2
unnamed: D2.1, SW2.2
unnamed: D3.1, SW3.2
unnamed: D4.1, SW4.2
unnamed: D5.1, SW5.2
unnamed: D6.1, SW6.2
unnamed: D7.1, SW7.2
unnamed: D8.1, SW8.2
unnamed: D9.1, SW9.2
unnamed: D10.1, SW10.2
unnamed: D11.1, SW11.2
unnamed: D12.1, SW12.2
unnamed: D13.1, SW13.2
unnamed: D14.1, SW14.2
unnamed: D15.1, SW15.2
unnamed: D16.1, SW16.2
unnamed: D17.1, SW17.2
unnamed: D18.1, SW18.2
unnamed: D19.1, SW19.2
unnamed: D20.1, SW20.2
unnamed: D21.1, SW21.2
unnamed: D22.1, SW22.2
unnamed: D23.1, SW23.2
unnamed: D24.1, SW24.2
unnamed: D25.1, SW25.2
unnamed: D26.1, SW26.2
unnamed: D27.1, SW27.2
unnamed: D28.1, SW28.2
unnamed: D29.1, SW29.2
unnamed: D30.1, SW30.2
unnamed: D31.1, SW31.2
unnamed: D32.1, SW32.2
unnamed: D33.1, SW33.2
unnamed: D34.1, SW34.2
unnamed: D35.1, SW35.2
unnamed: D36.1, SW36.2
unnamed: D37.1, SW37.2
unnamed: D38.1, SW38.2
unnamed: D39.1, SW39.2
SC: JP0.4, U0.16
SS: JP0.8, U0.17
VCC: JP0.1, U0.21
col0: SW0.1, SW10.1, SW20.1, SW30.1, U0.1
col1: SW1.1, SW11.1, SW21.1, SW31.1, U0.2
col2: SW2.1, SW12.1, SW22.1, SW32.1, U0.5
col3: SW3.1, SW13.1, SW23.1, SW33.1, U0.6
col4: SW4.1, SW14.1, SW24.1, SW34.1, U0.7
col5: SW5.1, SW15.1, SW25.1, SW35.1, U0.8
col6: SW6.1, SW16.1, SW26.1, SW36.1, U0.9
col7: SW7.1, SW17.1, SW27.1, SW37.1, U0.10
col8: SW8.1, SW18.1, SW28.1, SW38.1, U0.11
col9: SW9.1, SW19.1, SW29.1, SW39.1, U0.12
reset: RSSW0.1, U0.22
row0: D0.2, D1.2, D2.2, D3.2, D4.2, D5.2, D6.2, D7.2, D8.2, D9.2, U0.20
row1: D10.2, D11.2, D12.2, D13.2, D14.2, D15.2, D16.2, D17.2, D18.2, D19.2, U0.19
row2: D20.2, D21.2, D22.2, D23.2, D24.2, D25.2, D26.2, D27.2, D28.2, D29.2, U0.18
row3: D30.2, D31.2, D32.2, D33.2, D34.2, D35.2, D36.2, D37.2, D38.2, D39.2, U0.13

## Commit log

2020-10-19 for v1.1.0
2020-10-19 fill gnd and gnda
2020-10-29 create plate svg
2020-10-30 add choc version
2020-11-03 mod cutline and silk
2020-11-03 mod cutline and silk (#11)
2020-11-05 create logo
2020-11-05 paste logo to pcb
2020-11-05 13 create logo (#14)
    * create logo
    * paste logo to pcb
2020-11-07 mod for scatter42
2020-11-07 firmware for scatter42
2020-11-07 mod location of connector, open hole for protect panel and create default firmware (#18)
    * mod for scatter42
    * firmware for scatter42
2020-11-07 mod to allow to use kailh choc switch
2020-11-07 mod to allow to use kailh choc switch (#19)
2020-11-08 mod to cut at yushakobo
2020-11-08 mod plates of scatter42 for cutting at yushakobo (#20)
    * mod to allow to use kailh choc switch
    * mod to cut at yushakobo
2020-11-08 brushup firmware
2020-11-08 brushup firmware (#22)
2020-11-08 apply MIT LICENSE
2020-11-08 apply MIT LICENSE (#28)
2020-11-08 mod info.json
2020-11-09 Mod info json (#30)
    * mod info.json
    * mod info.json
2020-11-13 mod for v1.3.0
2020-11-13 mod readme
2020-11-15 create build guide
2020-11-15 create v1.2.0 build guide (#33)
    * create build guide
    * create build guide
    * create build guide
2020-11-15 add firmware build and install (#34)
    mod buildguide
2020-11-15 mod info.json and guide
2020-11-15 mod info.json and docs (#35)
2020-11-15 mod firmware readme
2020-11-15 mod firmware readme (#36)
2020-11-20 add sym lib
2020-12-04 add new keyboard -quantum-
2020-12-05 add readme for quantum
2020-12-05 mod readme for quantum
2020-12-06 mod plates data
2021-02-07 add quantum case and firmware
2021-02-07 New keyboard quantum (#38)
    * add new keyboard -quantum-
    * add readme for quantum
    * mod readme for quantum
    * mod plates data
    * add quantum case and firmware
2021-02-07 add new keyboard atom
2021-02-07 add new keyboard atom (#39)
2021-02-07 new keyboard atom-dactyl
2021-02-07 new keyboard atom-dactyl (#40)
2021-02-08 mod default keymap of atom
2021-02-08 mod atom default keymap (#41)
    * new keyboard atom-dactyl
    * mod default keymap of atom
2021-04-17 add new keyboard molecule
2021-04-17 add readme
2021-04-17 add new keyboard molecule (#42)
    * add new keyboard molecule
    * add readme
2021-04-17 New keyboard molecule (#43)
    * add new keyboard molecule
    * add readme
    * add readme
2021-04-17 mod image
2021-04-17 New keyboard molecule (#44)
    * add new keyboard molecule
    * add readme
    * add readme
    * mod image
2021-04-19 mod top-case
2021-04-19 mod molecule top case (#45)
    * add new keyboard molecule
    * add readme
    * add readme
    * mod image
    * mod top-case
2021-06-13 mod firmware and add top case and forms
2021-06-13 mod molecule firmware and add top plate, forms data (#46)
    * add new keyboard molecule
    * add readme
    * add readme
    * mod image
    * mod top-case
    * mod firmware and add top case and forms
2021-06-27 about keymap
2021-06-27 add about keymap for molecule keyboard
    * add about keymap
2021-07-10 init
2021-12-25 hagoromo wip
2021-12-25 dynamis
2021-12-26 dynamis wip
2021-12-28 gasket mount case
2021-12-30 update case
2021-12-30 add empty sch
2021-12-30 mod pro
2021-12-30 kicad version up to 6
2022-01-02 dynamis render
2022-01-03 mod case
2022-01-08 mod plate
2022-01-22 mod gitignore
2022-01-22 mod trackball
2022-01-22 mod skrew holes of weight
2022-02-25 add case form
